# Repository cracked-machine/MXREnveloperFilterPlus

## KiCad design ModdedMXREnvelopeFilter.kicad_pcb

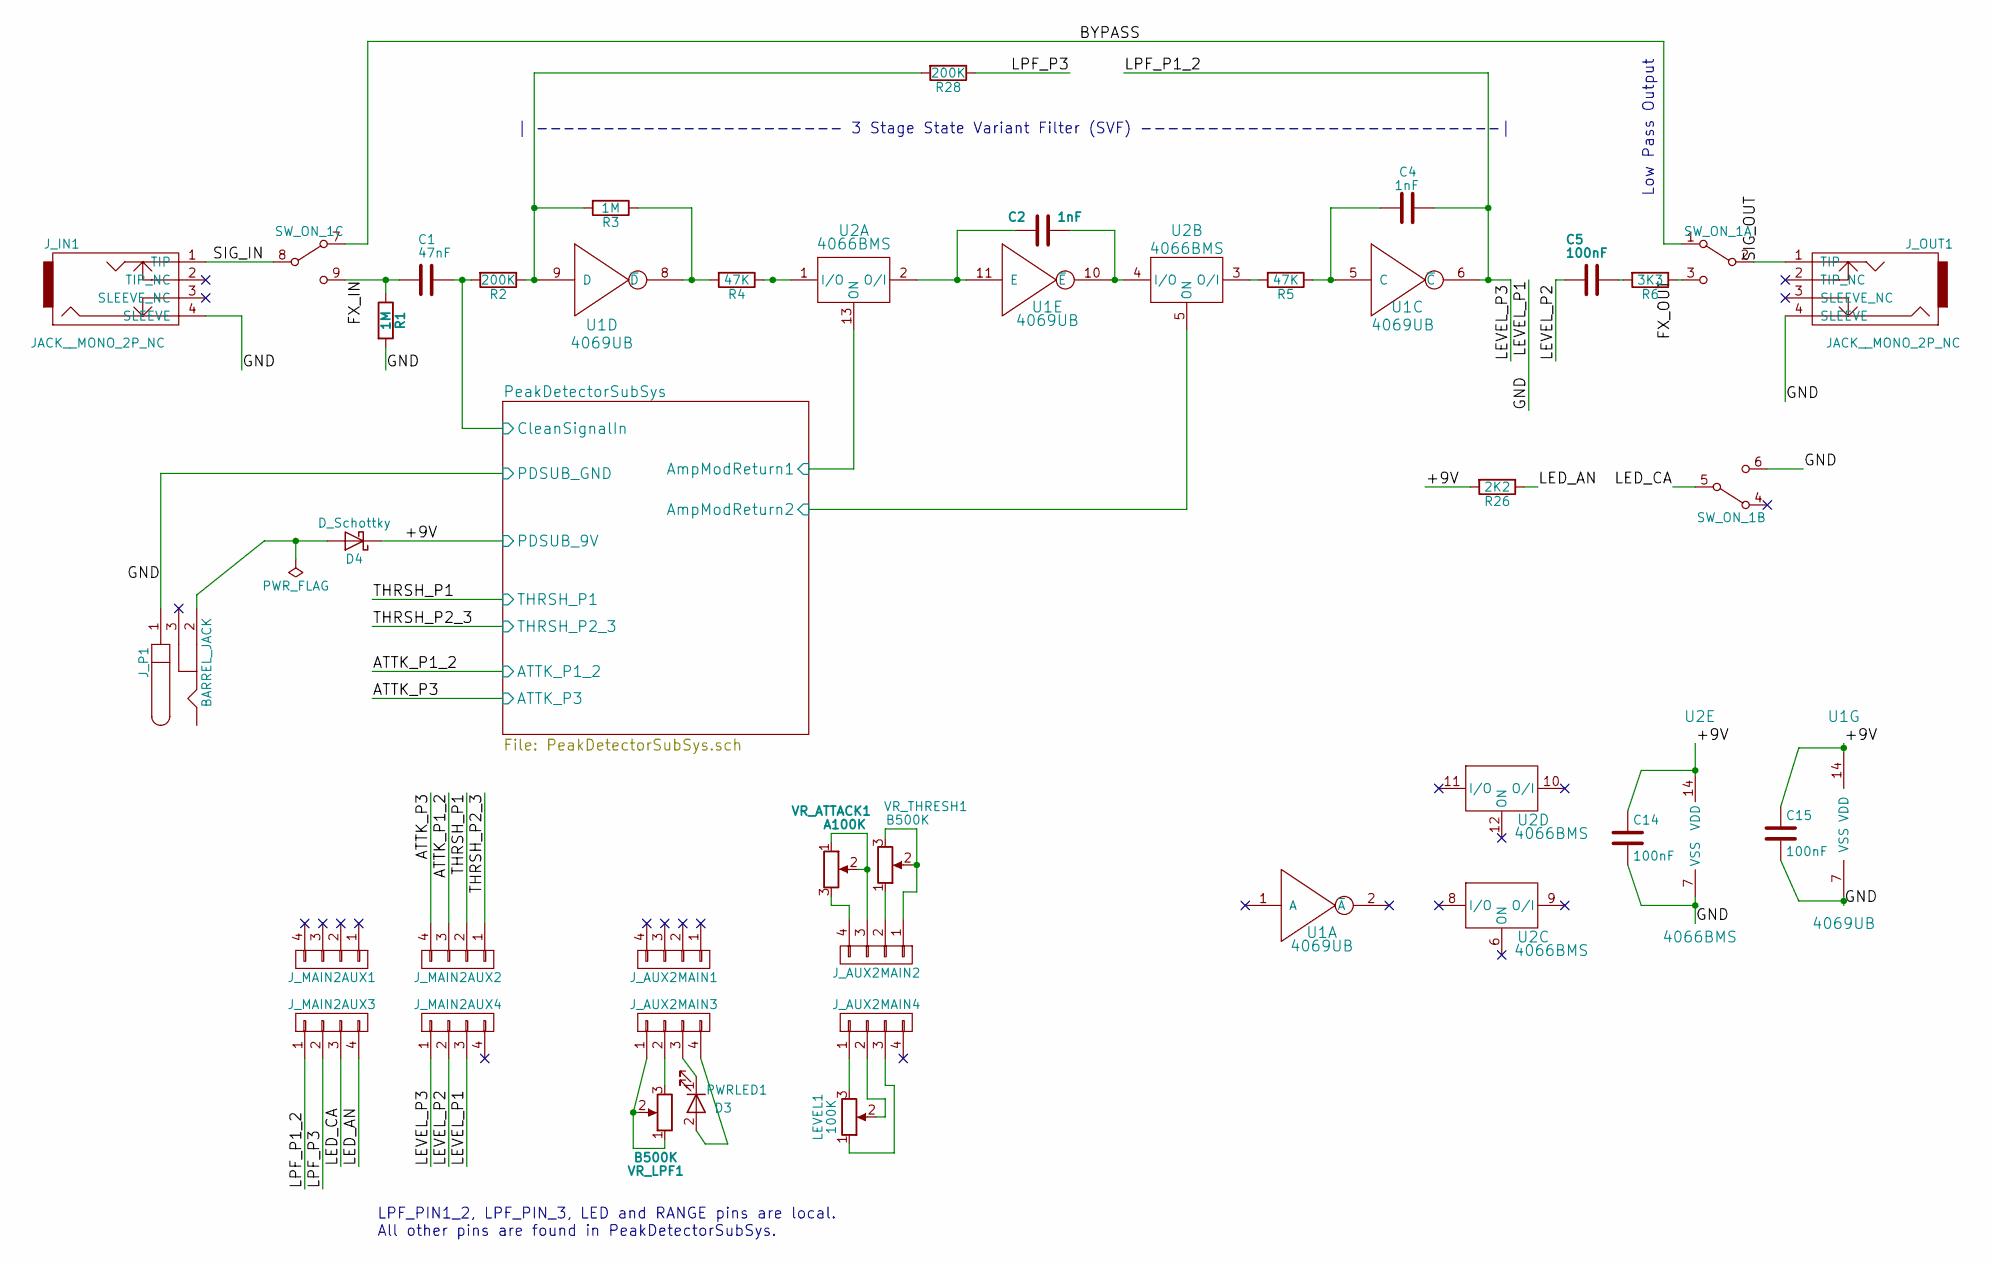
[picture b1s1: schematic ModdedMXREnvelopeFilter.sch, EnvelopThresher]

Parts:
C1: 47nF; C_0805_HandSoldering
C2, C4: 1nF; C_0805_HandSoldering
C5, C14, C15: 100nF; C_0805_HandSoldering
D3: PWRLED1; LED_D5.0mm
D4: D_Schottky; D_SOD-123
J_AUX2MAIN1, J_AUX2MAIN2, J_AUX2MAIN3, J_AUX2MAIN4: CONN_01X04; Pin_Header_Straight_1x04_Pitch2.54mm
J_IN1: JACK__MONO_2P_NC; NeutrikAudioSocket_Mono_PCB_NARROWPADS
J_MAIN2AUX1, J_MAIN2AUX2, J_MAIN2AUX3, J_MAIN2AUX4: CONN_01X04; Pin_Header_Straight_1x04_Pitch2.54mm
J_OUT1: JACK__MONO_2P_NC; NeutrikAudioSocket_Mono_PCB_NARROWPADS
J_P1: BARREL_JACK
LEVEL1: 100K; Potentiometer_Bourns_PTV09A-1_Horizontal
R1, R3: 1M; R_0805_HandSoldering
R2, R28: 200K; R_0805_HandSoldering
R4, R5: 47K; R_0805_HandSoldering
R6: 3K3; R_0805_HandSoldering
R26: 2K2; R_0805_HandSoldering
SW_ON_1: SW_3PDT_on_on; SW_3PDT_W18MM_L17.3MM_P5.3MM_D2MM_SolderLugs
U1: 4069UB; SOIC-14_3.9x8.7mm_Pitch1.27mm
U2: 4066BMS; SOIC-14_3.9x8.7mm_Pitch1.27mm
VR_ATTACK1: A100K; Potentiometer_Bourns_PTV09A-1_Horizontal
VR_LPF1: B500K; Potentiometer_Bourns_PTV09A-1_Horizontal
VR_THRESH1: B500K; Potentiometer_Bourns_PTV09A-1_Horizontal

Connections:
/+9V: C14.1, C15.1, D4.1 (K), R26.2, U1.14 (VDD), U2.14 (VDD); also elsewhere on the board
/ATTK_P1_2: J_MAIN2AUX2.3; also elsewhere on the board
/ATTK_P3: J_MAIN2AUX2.4; also elsewhere on the board
/BYPASS: SW_ON_1.1 (A), SW_ON_1.7 (A)
/FX_IN: C1.2, R1.1, SW_ON_1.9 (C)
/GND: C14.2, C15.2, J_IN1.4 (SLEEVE), J_MAIN2AUX4.3, J_OUT1.4 (SLEEVE), J_P1.1, R1.2, SW_ON_1.6 (C), U1.7 (VSS), U2.7 (VSS); also elsewhere on the board
/LED_AN: J_MAIN2AUX3.4, R26.1
/LED_CA: J_MAIN2AUX3.3, SW_ON_1.5 (B)
/LEVEL_P2: C5.2, J_MAIN2AUX4.2
/LEVEL_P3: C4.1, J_MAIN2AUX3.1, J_MAIN2AUX4.1, U1.6 (~C)
/LPF_P3: J_MAIN2AUX3.2, R28.1
/PeakDetectorSubSys/AmpModReturn1: U2.5 (ON), U2.13 (ON); also elsewhere on the board
/PeakDetectorSubSys/CleanSignalIn: C1.1, R2.2; also elsewhere on the board
/SIG_IN: J_IN1.1 (TIP), SW_ON_1.8 (B)
/SIG_OUT: J_OUT1.1 (TIP), SW_ON_1.2 (B)
/THRSH_P1: J_MAIN2AUX2.2; also elsewhere on the board
/THRSH_P2_3: J_MAIN2AUX2.1; also elsewhere on the board
unnamed: C2.1, U1.10 (~E), U2.4 (I/O)
unnamed: C2.2, U1.11 (E), U2.2 (O/I)
unnamed: C4.2, R5.1, U1.5 (C)
unnamed: C5.1, R6.2
unnamed: D3.1 (K), J_AUX2MAIN3.3
unnamed: D3.2 (A), J_AUX2MAIN3.4
unnamed: D4.2 (A), J_P1.2
unnamed: J_AUX2MAIN2.1, VR_THRESH1.2, VR_THRESH1.3
unnamed: J_AUX2MAIN2.2, VR_THRESH1.1
unnamed: J_AUX2MAIN2.3, VR_ATTACK1.1, VR_ATTACK1.2
unnamed: J_AUX2MAIN2.4, VR_ATTACK1.3
unnamed: J_AUX2MAIN3.1, VR_LPF1.1, VR_LPF1.2
unnamed: J_AUX2MAIN3.2, VR_LPF1.3
unnamed: J_AUX2MAIN4.1, LEVEL1.3
unnamed: J_AUX2MAIN4.2, LEVEL1.2
unnamed: J_AUX2MAIN4.3, LEVEL1.1
unnamed: R2.1, R3.2, R28.2, U1.9 (D)
unnamed: R3.1, R4.2, U1.8 (~D)
unnamed: R4.1, U2.1 (I/O)
unnamed: R5.2, U2.3 (O/I)
unnamed: R6.1, SW_ON_1.3 (C)

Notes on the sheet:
| ----------------------- 3 Stage State Variant Filter (SVF) ---------------------------|
Low Pass Output
LPF_PIN1_2, LPF_PIN_3, LED and RANGE pins are local. All other pins are found in PeakDetectorSubSys.

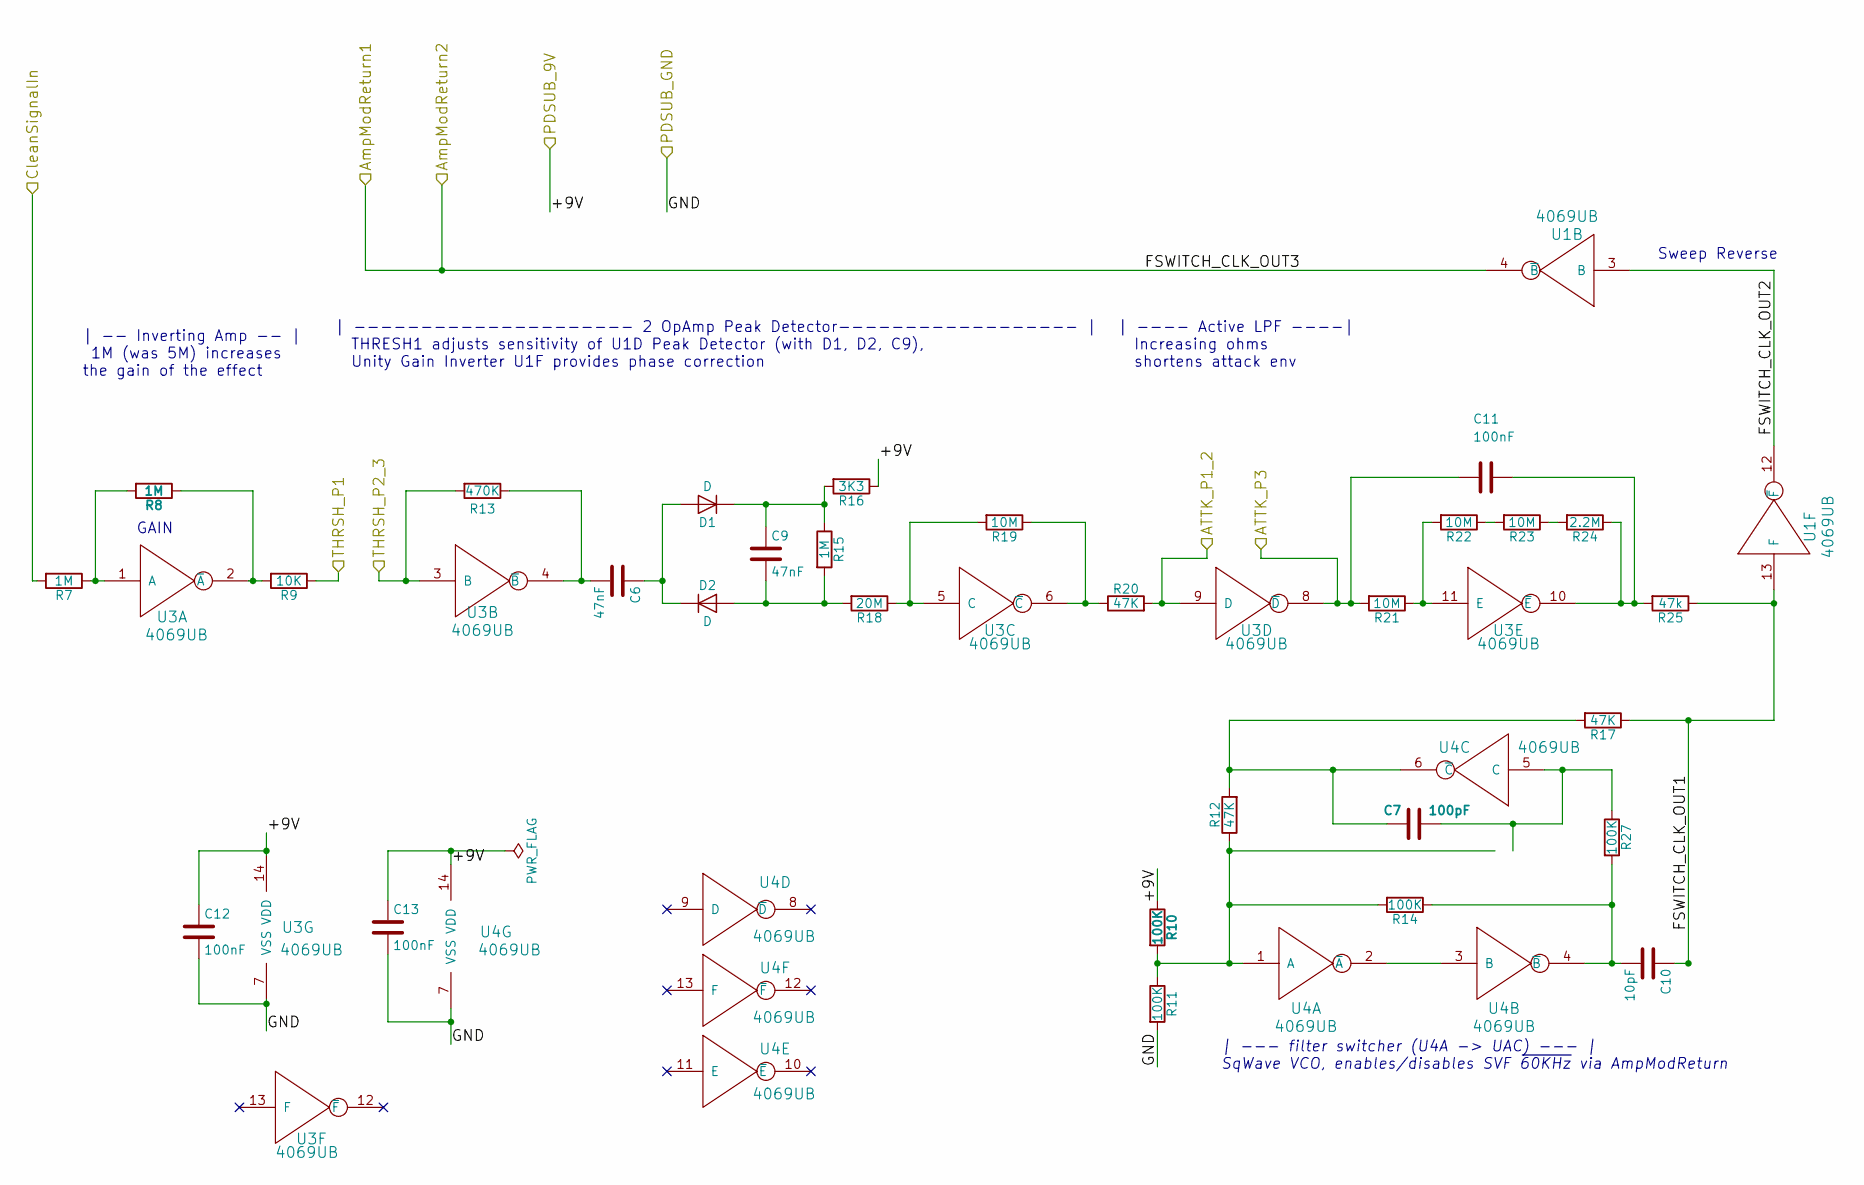
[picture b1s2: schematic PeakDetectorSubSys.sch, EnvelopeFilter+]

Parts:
C6, C9: 47nF; C_0805_HandSoldering
C7: 100pF; C_0805_HandSoldering
C10: 10pF; C_0805_HandSoldering
C11, C12, C13: 100nF; C_0805_HandSoldering
D1, D2: D; D_SOD-123
R7, R8, R15: 1M; R_0805_HandSoldering
R9: 10K; R_0805_HandSoldering
R10, R11, R14, R27: 100K; R_0805_HandSoldering
R12, R17, R20: 47K; R_0805_HandSoldering
R13: 470K; R_0805_HandSoldering
R16: 3K3; R_0805_HandSoldering
R18: 20M; R_0805_HandSoldering
R19, R21, R22, R23: 10M; R_0805_HandSoldering
R24: 2.2M; R_0805_HandSoldering
R25: 47k; R_0805_HandSoldering
U1, U3, U4: 4069UB; SOIC-14_3.9x8.7mm_Pitch1.27mm

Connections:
/+9V: C12.1, C13.1, R10.1, R16.1, U3.14 (VDD), U4.14 (VDD); also elsewhere on the board
/ATTK_P1_2: R20.2, U3.9 (D); also elsewhere on the board
/ATTK_P3: C11.2, R21.2, U3.8 (~D); also elsewhere on the board
/GND: C12.2, C13.2, R11.2, U3.7 (VSS), U4.7 (VSS); also elsewhere on the board
/PeakDetectorSubSys/AmpModReturn1: U1.4 (~B); also elsewhere on the board
/PeakDetectorSubSys/CleanSignalIn: R7.2; also elsewhere on the board
/PeakDetectorSubSys/FSWITCH_CLK_OUT1: C10.1, R17.1, R25.1, U1.13 (F)
/PeakDetectorSubSys/FSWITCH_CLK_OUT2: U1.3 (B), U1.12 (~F)
/THRSH_P1: R9.1; also elsewhere on the board
/THRSH_P2_3: R13.2, U3.3 (B); also elsewhere on the board
unnamed: C6.1, D1.2 (A), D2.1 (K)
unnamed: C6.2, R13.1, U3.4 (~B)
unnamed: C7.1, R27.1, U4.5 (C)
unnamed: C7.2, R12.2, R17.2, U4.6 (~C)
unnamed: C9.1, D1.1 (K), R15.1, R16.2
unnamed: C9.2, D2.2 (A), R15.2, R18.2
unnamed: C10.2, R14.1, R27.2, U4.4 (~B)
unnamed: C11.1, R24.1, R25.2, U3.10 (~E)
unnamed: R7.1, R8.2, U3.1 (A)
unnamed: R8.1, R9.2, U3.2 (~A)
unnamed: R10.2, R11.1, R12.1, R14.2, U4.1 (A)
unnamed: R18.1, R19.2, U3.5 (C)
unnamed: R19.1, R20.1, U3.6 (~C)
unnamed: R21.1, R22.2, U3.11 (E)
unnamed: R22.1, R23.2
unnamed: R23.1, R24.2
unnamed: U4.2 (~A), U4.3 (B)

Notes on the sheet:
| ---- Active LPF ----| Increasing ohms shortens attack env
Sweep Reverse
| --------------------- 2 OpAmp Peak Detector------------------ | THRESH1 adjusts sensitivity of U1D Peak Detector (with D1, D2, C9), Unity Gain Inverter U1F provides phase correction
| --- filter switcher (U4A -> UAC) --- | SqWave VCO, enables/disables SVF ~60KHz via AmpModReturn
| -- Inverting Amp -- | 1M (was 5M) increases the gain of the effect
GAIN

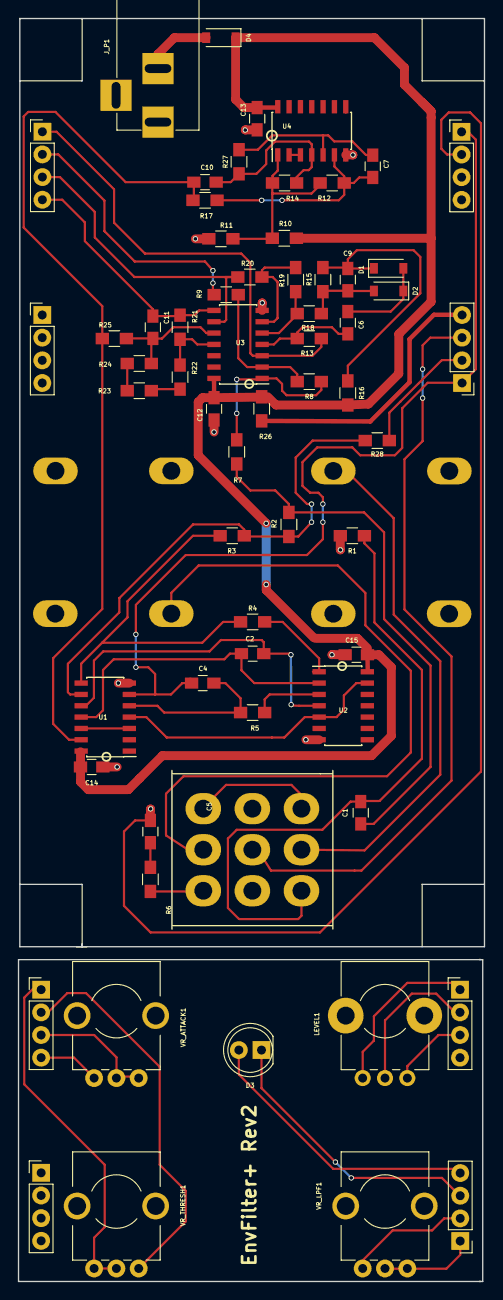
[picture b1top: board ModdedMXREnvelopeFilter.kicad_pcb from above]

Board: 2 copper layers, 52.2 x 141.5 mm, 65 parts (0 on the bottom side), 57 nets.
